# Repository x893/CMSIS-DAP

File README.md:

CMSIS-DAP Version 0.01
----------------------

See Readme.htm for details

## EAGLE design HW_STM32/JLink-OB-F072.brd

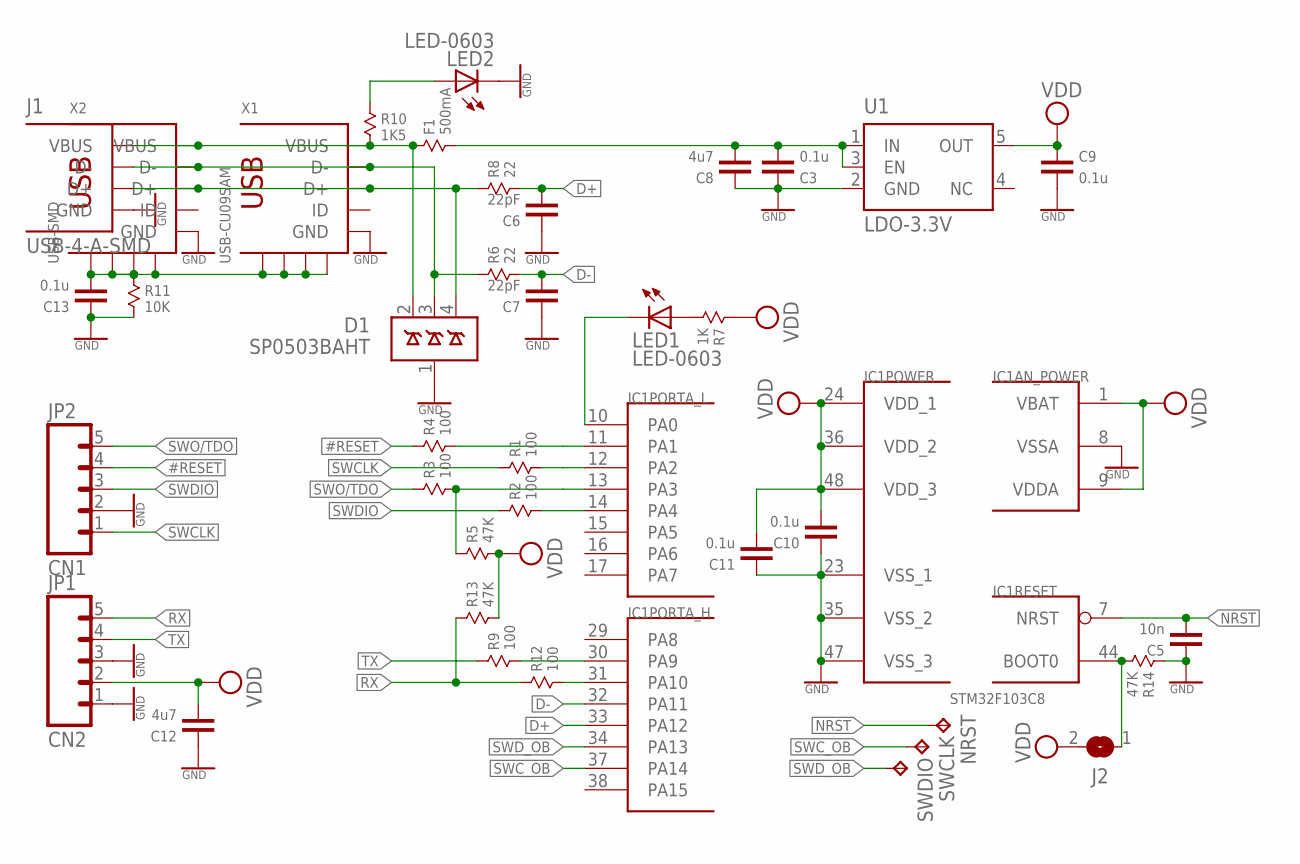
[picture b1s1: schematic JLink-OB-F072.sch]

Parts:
C3, C9, C10, C11, C13: 0.1u; 0603
C5: 10n; 0603
C6, C7: 22pF; 0603
C8, C12: 4u7; 0603
D1: SP0503BAHT; SOT143
F1: 500mA; 0805
IC1: STM32F103C8; TQFP48
J1: USB-4-A-SMD; USB-A-SMD
J2: JUMPER2-0402-NC; JUMPER2-0402_NC
JP1: CN2; 1X05
JP2: CN1; 1X05
LED1, LED2: LED-0603; CHIPLED_0603
NRST: TPTP10R; TP10R
R1, R2, R3, R4, R9, R12: 100; 0603
R5, R13, R14: 47K; 0603
R6, R8: 22; 0603
R7: 1K; 0603
R10: 1K5; 0603
R11: 10K; 0603
SWCLK: TPTP10R; TP10R
SWDIO: TPTP10R; TP10R
U1: LDO-3.3V; SOT23-5
X1: USB-CU09SAM; CU09SAM
X2: USB-SMD; USB-MINIB

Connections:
#RESET: JP2.4, R4.1
#RESETR: IC1.11 (PA1), R4.2
D+: C6.1, IC1.33 (PA12), R8.2
D-: C7.1, IC1.32 (PA11), R6.2
GND: C3.2, C5.2, C6.2, C7.2, C8.2, C9.1, C10.2, C11.2, C12.2, C13.2, D1.1 (GND), IC1.8 (VSSA), IC1.23 (VSS_1), IC1.35 (VSS_2), IC1.47 (VSS_3), J1.GND, JP1.1, JP1.3, JP2.2, LED2.C, R11.2, R14.1, U1.2 (GND), X1.5 (GND), X2.GND
unnamed: LED1.A, R7.2
unnamed: D1.4 (D3), J1.D+, R8.1, X1.3 (D+), X2.D+
unnamed: IC1.10 (PA0), LED1.C
unnamed: D1.3 (D2), J1.D-, R6.1, X1.2 (D-), X2.D-
unnamed: IC1.30 (PA9), R9.2
unnamed: IC1.31 (PA10), R12.2
unnamed: LED2.A, R10.1
unnamed: C3.1, C8.1, F1.2, U1.1 (IN), U1.3 (EN)
unnamed: IC1.44 (BOOT0), J2.1, R14.2
unnamed: C13.1, R11.1, X1.GND@1 (GND), X1.GND@2 (GND), X1.GND@3 (GND), X1.GND@4 (GND), X2.GND@1 (GND), X2.GND@2 (GND), X2.GND@3 (GND), X2.GND@4 (GND)
NRST: C5.1, IC1.7 (NRST), NRST.TP
RX: JP1.5, R12.1, R13.1
SWCLK: JP2.1, R1.1
SWCLKR: IC1.12 (PA2), R1.2
SWC_OB: IC1.37 (PA14), SWCLK.TP
SWDIO: JP2.3, R2.1
SWDIOR: IC1.14 (PA4), R2.2
SWD_OB: IC1.34 (PA13), SWDIO.TP
SWO/TDO: JP2.5, R3.1
SWOR: IC1.13 (PA3), R3.2, R5.1
TX: JP1.4, R9.1
VBUS: D1.2 (D1), F1.1, J1.VUSB (VBUS), R10.2, X1.1 (VBUS), X2.VBUS
VDD: C9.2, C10.1, C11.1, C12.1, IC1.1 (VBAT), IC1.9 (VDDA), IC1.24 (VDD_1), IC1.36 (VDD_2), IC1.48 (VDD_3), J2.2, JP1.2, R5.2, R7.1, R13.2, U1.5 (OUT)

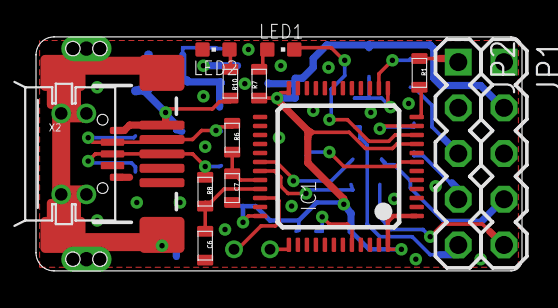
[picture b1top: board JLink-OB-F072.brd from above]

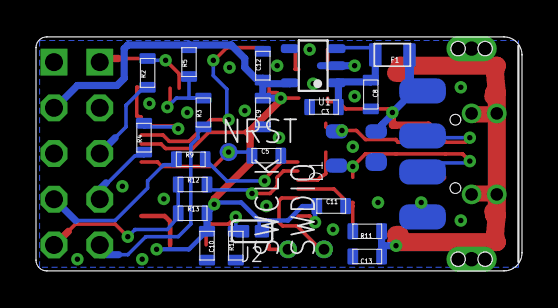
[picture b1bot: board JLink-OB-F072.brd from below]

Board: 2 copper layers, 27.0 x 13.0 mm, 39 parts (25 on the bottom side), 28 nets.

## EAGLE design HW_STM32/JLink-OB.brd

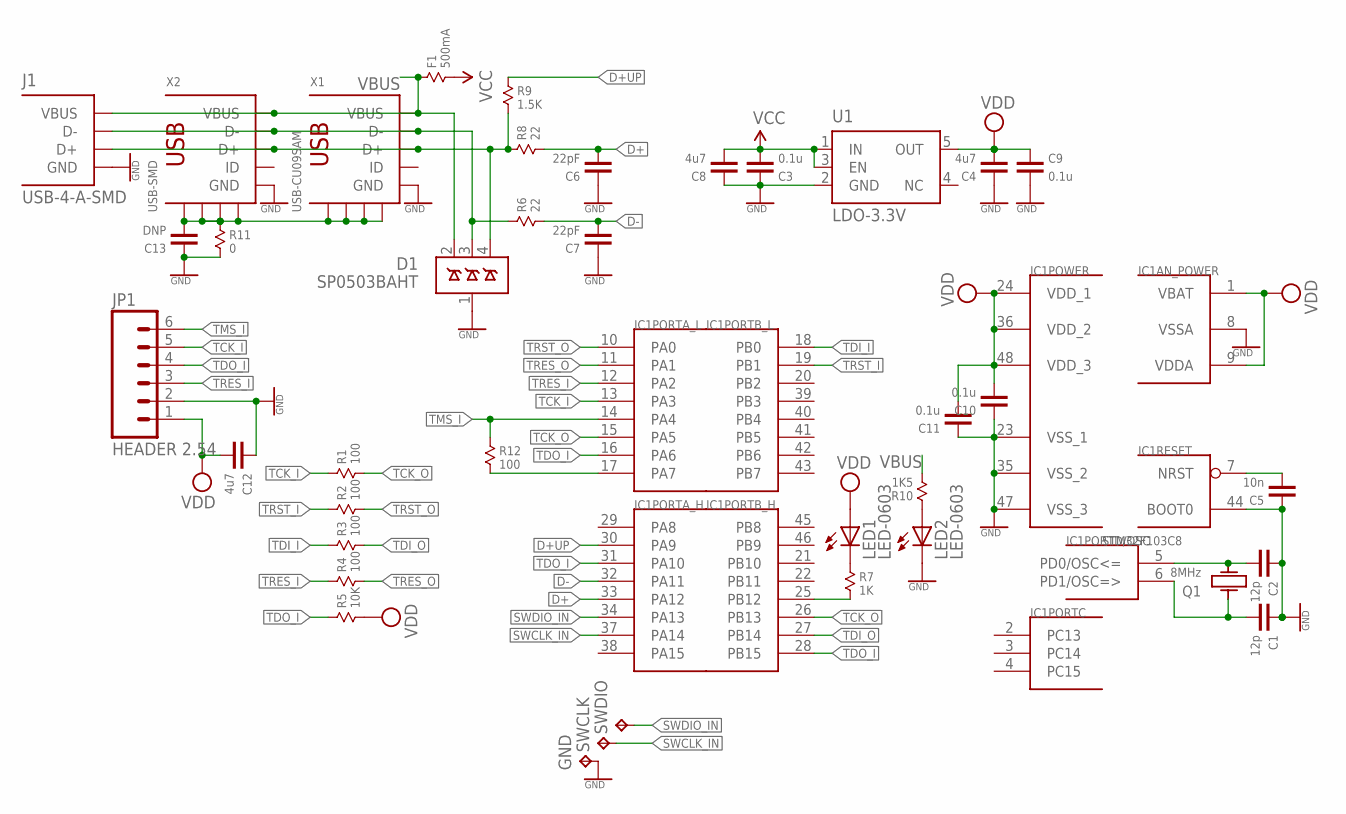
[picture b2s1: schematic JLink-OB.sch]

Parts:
C1, C2: 12p; 0603
C3, C9, C10, C11: 0.1u; 0603
C4, C8, C12: 4u7; 0603
C5: 10n; 0603
C6, C7: 22pF; 0603
C13: DNP; 0603
D1: SP0503BAHT; SOT143
F1: 500mA; 0805
GND: TPTP12R; TP12R
IC1: STM32F103C8; TQFP48
J1: USB-4-A-SMD; USB-A-SMD
JP1: HEADER 2.54; 1X06
LED1, LED2: LED-0603; CHIPLED_0603
Q1: 8MHz; KX-9A
R1, R2, R3, R4, R12: 100; 0603
R5: 10K; 0603
R6, R8: 22; 0603
R7: 1K; 0603
R9: 1.5K; 0603
R10: 1K5; 0603
R11: 0; 0603
SWCLK: TPTP12R; TP12R
SWDIO: TPTP12R; TP12R
U1: LDO-3.3V; SOT23-5
X1: USB-CU09SAM; CU09SAM
X2: USB-SMD; USB-MINIB

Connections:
D+: C6.1, IC1.33 (PA12), R8.2
D+UP: IC1.30 (PA9), R9.1
D-: C7.1, IC1.32 (PA11), R6.2
GND: C1.2, C2.2, C3.2, C4.2, C5.2, C6.2, C7.2, C8.2, C9.1, C10.2, C11.2, C12.2, C13.2, D1.1 (GND), GND.TP, IC1.8 (VSSA), IC1.23 (VSS_1), IC1.35 (VSS_2), IC1.44 (BOOT0), IC1.47 (VSS_3), J1.GND, JP1.2, LED2.C, R11.2, U1.2 (GND), X1.5 (GND), X2.GND
unnamed: C5.1, IC1.7 (NRST)
unnamed: D1.4 (D3), J1.D+, R8.1, R9.2, X1.3 (D+), X2.D+
unnamed: IC1.25 (PB12), R7.2
unnamed: D1.3 (D2), J1.D-, R6.1, X1.2 (D-), X2.D-
unnamed: C2.1, IC1.5 (PD0/OSC<=), Q1.3 (2)
unnamed: C1.1, IC1.6 (PD1/OSC=>), Q1.1
unnamed: LED2.A, R10.1
unnamed: LED1.C, R7.1
unnamed: C13.1, R11.1, X1.GND@1 (GND), X1.GND@2 (GND), X1.GND@3 (GND), X1.GND@4 (GND), X2.GND@1 (GND), X2.GND@2 (GND), X2.GND@3 (GND), X2.GND@4 (GND)
SWCLK_IN: IC1.37 (PA14), SWCLK.TP
SWDIO_IN: IC1.34 (PA13), SWDIO.TP
TCK_I: IC1.13 (PA3), JP1.5, R1.1
TCK_O: IC1.15 (PA5), IC1.26 (PB13), R1.2
TDI_I: IC1.18 (PB0), R3.1
TDI_O: IC1.27 (PB14), R3.2
TDO_I: IC1.16 (PA6), IC1.28 (PB15), IC1.31 (PA10), JP1.4, R5.1
TMS_I: IC1.14 (PA4), JP1.6, R12.1
TMS_O: IC1.17 (PA7), R12.2
TRES_I: IC1.12 (PA2), JP1.3, R4.1
TRES_O: IC1.11 (PA1), R4.2
TRST_I: IC1.19 (PB1), R2.1
TRST_O: IC1.10 (PA0), R2.2
VBUS: D1.2 (D1), F1.1, J1.VUSB (VBUS), R10.2, X1.1 (VBUS), X2.VBUS
VCC: C3.1, C8.1, F1.2, U1.1 (IN), U1.3 (EN)
VDD: C4.1, C9.2, C10.1, C11.1, C12.1, IC1.1 (VBAT), IC1.9 (VDDA), IC1.24 (VDD_1), IC1.36 (VDD_2), IC1.48 (VDD_3), JP1.1, LED1.A, R5.2, U1.5 (OUT)

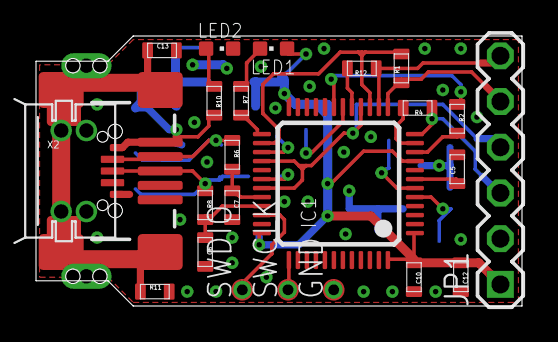
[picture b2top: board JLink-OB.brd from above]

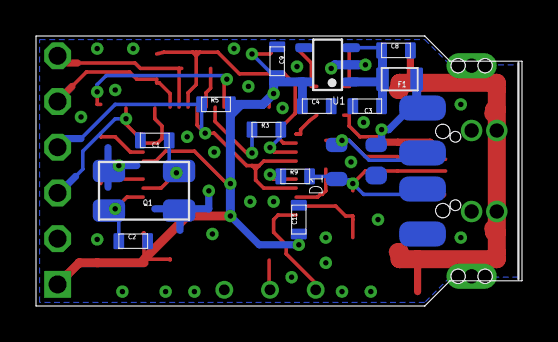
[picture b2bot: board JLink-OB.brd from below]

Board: 2 copper layers, 27.0 x 15.0 mm, 39 parts (15 on the bottom side), 29 nets.

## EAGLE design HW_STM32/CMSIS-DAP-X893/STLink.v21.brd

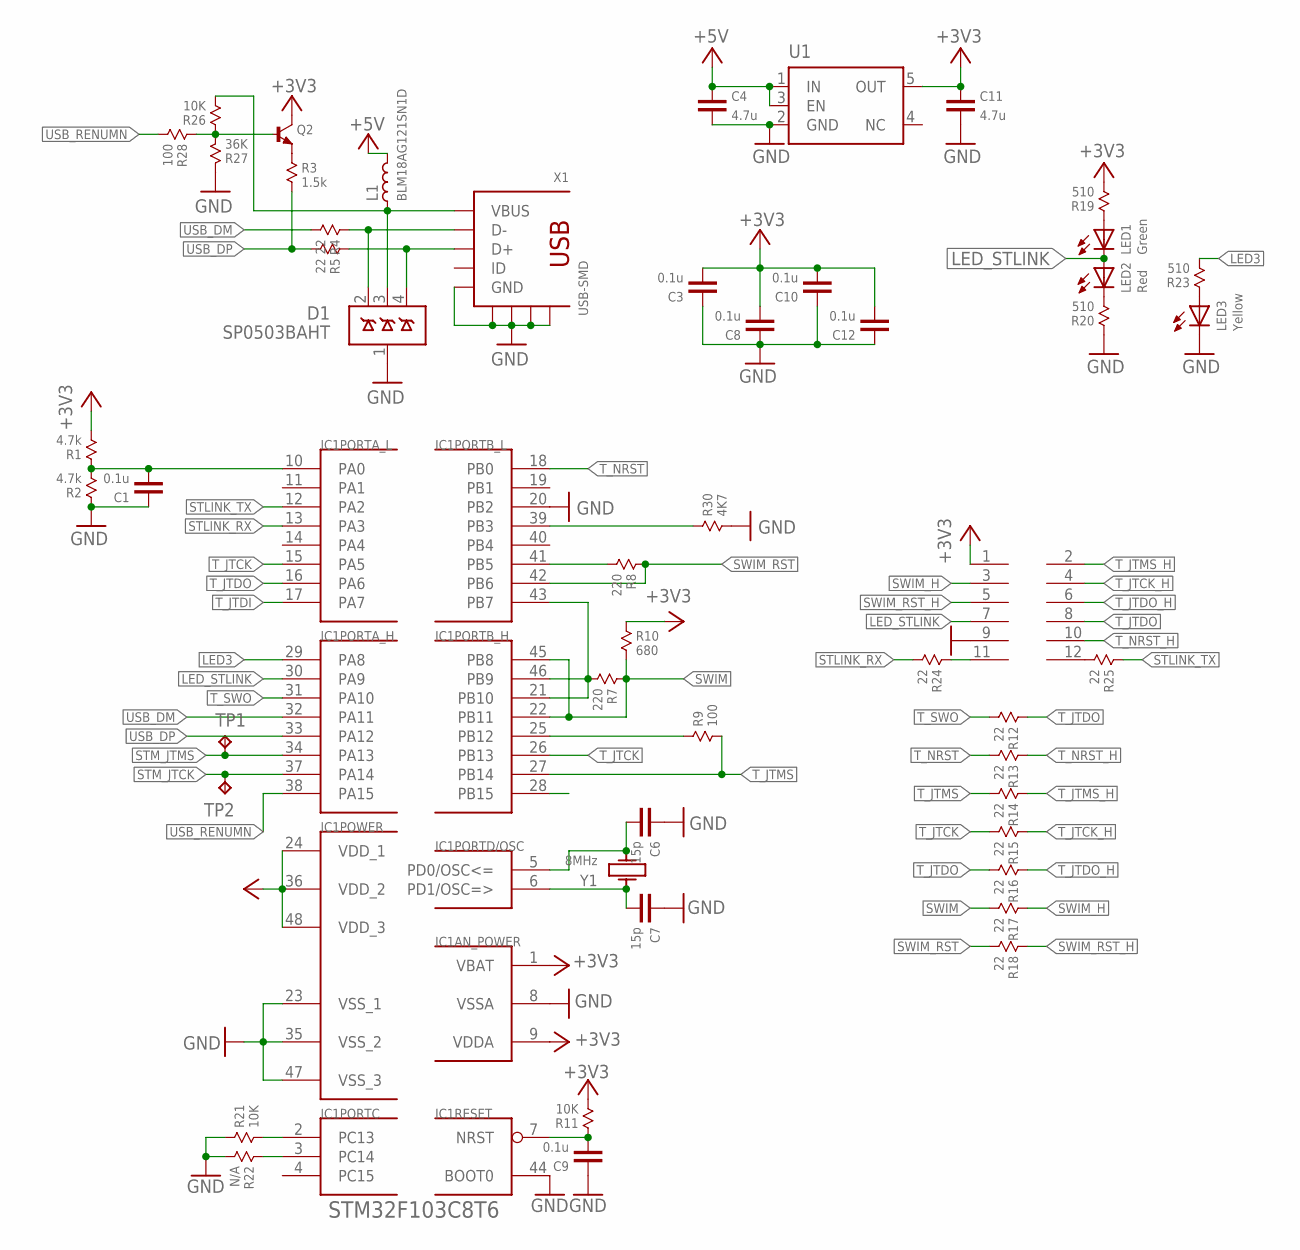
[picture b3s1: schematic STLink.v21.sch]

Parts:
C1, C3, C8, C9, C10, C12: 0.1u; 0603
C4, C11: 4.7u; 0603
C6, C7: 15p; 0603
CN2: M06X2; PLANAR-6X2
D1: SP0503BAHT; SOT143
IC1: STM32F103C8T6; TQFP48
L1: BLM18AG121SN1D; 0603
LED1: Green; CHIP-LED0603
LED2: Red; CHIP-LED0603
LED3: Yellow; CHIP-LED0603
Q2: NPNBC847; SOT-23
R1, R2: 4.7k; 0603
R3: 1.5k; 0603
R4, R5, R12, R13, R14, R15, R16, R17, R18, R24, R25: 22; 0603
R7, R8: 220; 0603
R9, R28: 100; 0603
R10: 680; 0603
R11, R21, R26: 10K; 0603
R19, R20, R23: 510; 0603
R22: N/A; 0603
R27: 36K; 0603
R30: 4K7; 0603
TP1, TP2: TPTP10R; TP10R
U1: TPS73033; SOT23-5
X1: USB-SMD; USB-MINIB
Y1: 8MHz; C0532

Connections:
+3V3: C3.1, C8.1, C10.1, C11.2, C12.1, CN2.1, IC1.1 (VBAT), IC1.9 (VDDA), IC1.24 (VDD_1), IC1.36 (VDD_2), IC1.48 (VDD_3), Q2.3 (C), R1.2, R10.1, R11.2, R19.2, U1.5 (OUT)
+5V: C4.2, L1.2, U1.1 (IN), U1.3 (EN)
AIN1: C1.1, IC1.10 (PA0), R1.1, R2.2
GND: C1.2, C3.2, C4.1, C6.2, C7.2, C8.2, C9.2, C10.2, C11.1, C12.2, CN2.9, D1.1 (GND), IC1.8 (VSSA), IC1.20 (PB2), IC1.23 (VSS_1), IC1.35 (VSS_2), IC1.44 (BOOT0), IC1.47 (VSS_3), LED3.C, R2.1, R20.1, R21.1, R22.2, R27.1, R30.2, U1.2 (GND), X1.GND, X1.GND@1 (GND), X1.GND@2 (GND), X1.GND@3 (GND), X1.GND@4 (GND)
LED3: IC1.29 (PA8), R23.2
LED_STLINK: CN2.7, IC1.30 (PA9), LED1.C, LED2.A
unnamed: C6.1, IC1.5 (PD0/OSC<=), Y1.3 (2)
unnamed: C7.1, IC1.6 (PD1/OSC=>), Y1.1
unnamed: C9.1, IC1.7 (NRST), R11.1
unnamed: IC1.39 (PB3), R30.1
unnamed: D1.2 (D1), R4.1, X1.D-
unnamed: D1.4 (D3), R5.1, X1.D+
unnamed: LED2.C, R20.2
unnamed: LED1.A, R19.1
unnamed: D1.3 (D2), L1.1, R26.2, X1.VBUS
unnamed: CN2.11, R24.1
unnamed: CN2.12, R25.2
unnamed: LED3.A, R23.1
unnamed: Q2.2 (E), R3.1
unnamed: IC1.2 (PC13), R21.2
unnamed: IC1.3 (PC14), R22.1
unnamed: Q2.1 (B), R26.1, R27.2, R28.1
STLINK_RX: IC1.13 (PA3), R24.2
STLINK_TX: IC1.12 (PA2), R25.1
STM_JTCK: IC1.37 (PA14), TP2.TP
STM_JTMS: IC1.34 (PA13), TP1.TP
SWIM: IC1.22 (PB11), IC1.45 (PB8), R7.1, R10.2, R17.2
SWIM_H: CN2.3, R17.1
SWIM_IN: IC1.21 (PB10), IC1.43 (PB7), IC1.46 (PB9), R7.2
SWIM_RST: IC1.42 (PB6), R8.1, R18.2
SWIM_RST_H: CN2.5, R18.1
SWIM_RST_IN: IC1.41 (PB5), R8.2
T_JTCK: IC1.15 (PA5), IC1.26 (PB13), R15.2
T_JTCK_H: CN2.4, R15.1
T_JTDI: IC1.17 (PA7)
T_JTDO: CN2.8, IC1.16 (PA6), R12.1, R16.2
T_JTDO_H: CN2.6, R16.1
T_JTMS: IC1.27 (PB14), R9.2, R14.2
T_JTMS_H: CN2.2, R14.1
T_NRST: IC1.18 (PB0), R13.2
T_NRST_H: CN2.10, R13.1
T_SWDIO_IN: IC1.25 (PB12), R9.1
T_SWO: IC1.31 (PA10), R12.2
USB_DM: IC1.32 (PA11), R4.2
USB_DP: IC1.33 (PA12), R3.2, R5.2
USB_RENUMN: IC1.38 (PA15), R28.2

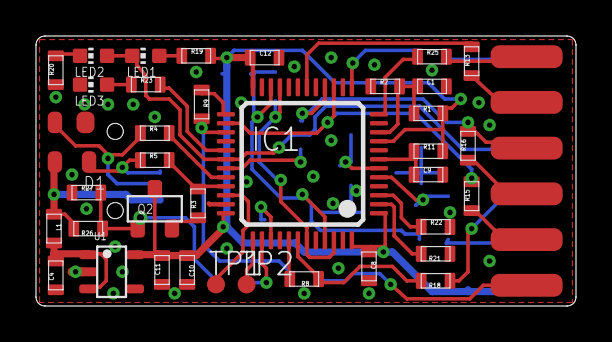
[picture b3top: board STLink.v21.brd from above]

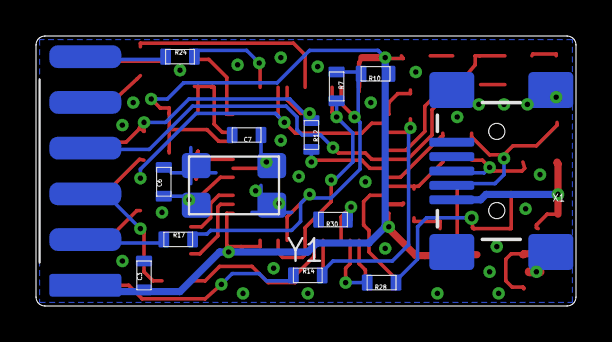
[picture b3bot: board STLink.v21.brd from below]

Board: 2 copper layers, 30.0 x 15.0 mm, 51 parts (14 on the bottom side), 45 nets.

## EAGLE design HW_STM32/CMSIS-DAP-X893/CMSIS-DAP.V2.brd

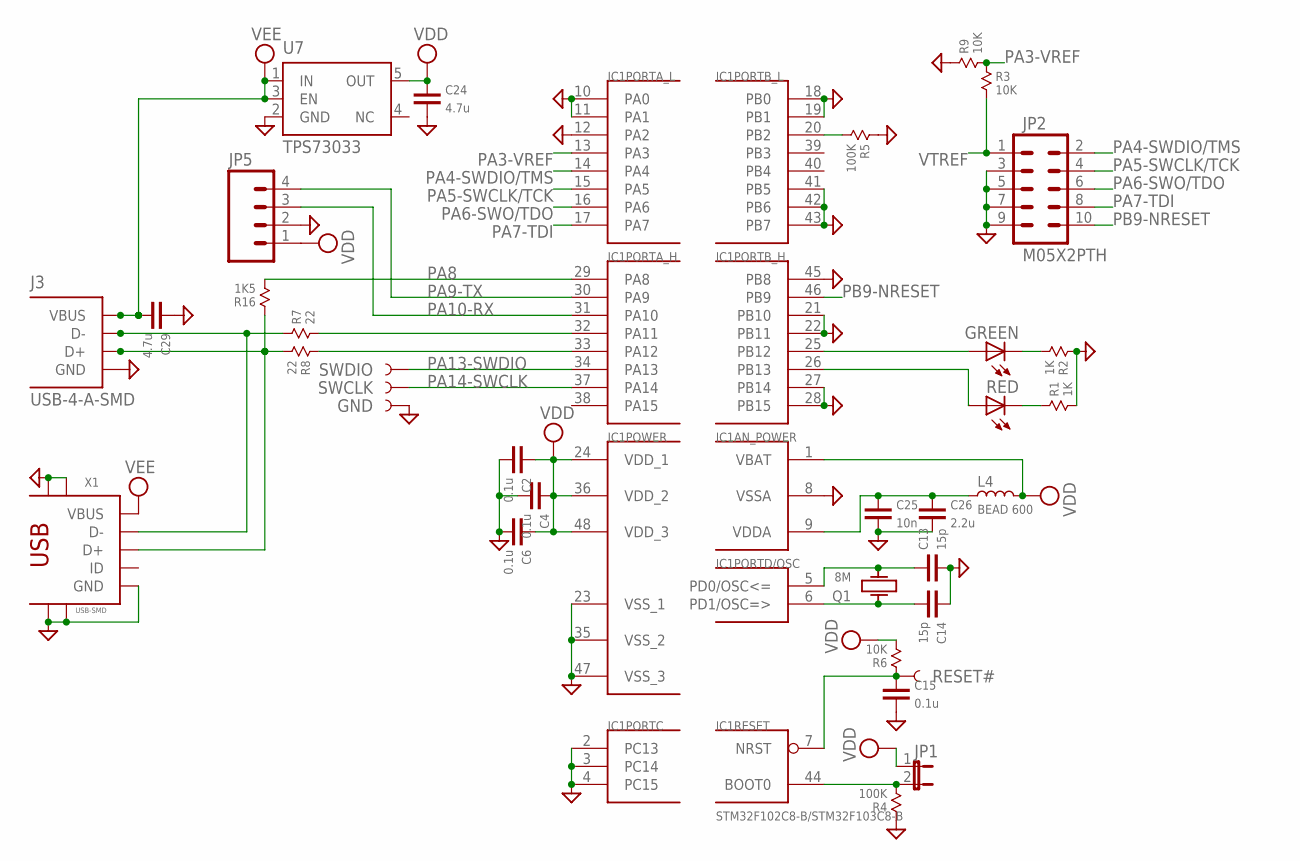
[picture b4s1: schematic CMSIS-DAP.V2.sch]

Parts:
C2, C4, C6, C15: 0.1u; 0603
C13, C14: 15p; 0603
C24, C29: 4.7u; 0603
C25: 10n; 0603
C26: 2.2u; 0603
GND: TEST-POINT1; PAD.1X1
GREEN: LEDCHIPLED_0603; CHIPLED_0603
IC1: STM32F102C8-B/STM32F103C8-B; TQFP48
J3: USB-4-A-SMD; USB-A-SMD
JP1: JUMPER-2SMD-NO; SJ_2S-NO
JP2: M05X2PTH; AVR_ICSP
JP5: M04PTH; 1X04
L4: BEAD 600; 0603
Q1: 8M; KX-9A
R1, R2: 1K; 0603
R3, R6, R9: 10K; 0603
R4, R5: 100K; 0603
R7, R8: 22; 0603
R16: 1K5; 0603
RED: LEDCHIPLED_0603; CHIPLED_0603
RESET#: TEST-POINT3; PAD.03X.03
SWCLK: TEST-POINT1; PAD.1X1
SWDIO: TEST-POINT1; PAD.1X1
U7: TPS73033; SOT23-5
X1: USB-SMD; USB-MINIB

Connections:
BOOT0: IC1.44 (BOOT0), JP1.2, R4.2
GND: C2.1, C4.1, C6.1, C13.1, C14.2, C15.1, C24.1, C25.1, C26.1, C29.2, GND.P$1, IC1.2 (PC13), IC1.3 (PC14), IC1.4 (PC15), IC1.8 (VSSA), IC1.10 (PA0), IC1.11 (PA1), IC1.12 (PA2), IC1.18 (PB0), IC1.19 (PB1), IC1.21 (PB10), IC1.22 (PB11), IC1.23 (VSS_1), IC1.27 (PB14), IC1.28 (PB15), IC1.35 (VSS_2), IC1.41 (PB5), IC1.42 (PB6), IC1.43 (PB7), IC1.45 (PB8), IC1.47 (VSS_3), J3.GND, JP2.3, JP2.5, JP2.7, JP2.9, JP5.2, R1.2, R2.1, R4.1, R5.1, R9.1, U7.2 (GND), X1.GND, X1.GND@1 (GND), X1.GND@2 (GND), X1.GND@3 (GND), X1.GND@4 (GND)
unnamed: R1.1, RED.C
unnamed: C25.2, C26.2, IC1.9 (VDDA), L4.1
unnamed: J3.D-, R7.1, X1.D-
unnamed: GREEN.C, R2.2
unnamed: J3.D+, R8.2, R16.1, X1.D+
OSCIN: C14.1, IC1.6 (PD1/OSC=>), Q1.1
OSCOUT: C13.2, IC1.5 (PD0/OSC<=), Q1.3 (2)
PA3-VREF: IC1.13 (PA3), R3.1, R9.2
PA4-SWDIO/TMS: IC1.14 (PA4), JP2.2
PA5-SWCLK/TCK: IC1.15 (PA5), JP2.4
PA6-SWO/TDO: IC1.16 (PA6), JP2.6
PA7-TDI: IC1.17 (PA7), JP2.8
PA8: IC1.29 (PA8), R16.2
PA9-TX: IC1.30 (PA9), JP5.4
PA10-RX: IC1.31 (PA10), JP5.3
PA11: IC1.32 (PA11), R7.2
PA12: IC1.33 (PA12), R8.1
PA13-SWDIO: IC1.34 (PA13), SWDIO.P$1
PA14-SWCLK: IC1.37 (PA14), SWCLK.P$1
PB2/BOOT1: IC1.20 (PB2), R5.2
PB9-NRESET: IC1.46 (PB9), JP2.10
PB12: GREEN.A, IC1.25 (PB12)
PB13: IC1.26 (PB13), RED.A
RESET#: C15.2, IC1.7 (NRST), R6.1, RESET#.P$1
VDD: C2.2, C4.2, C6.2, C24.2, IC1.1 (VBAT), IC1.24 (VDD_1), IC1.36 (VDD_2), IC1.48 (VDD_3), JP1.1, JP5.1, L4.2, R6.2, U7.5 (OUT)
VEE: C29.1, J3.VUSB (VBUS), U7.1 (IN), U7.3 (EN), X1.VBUS
VTREF: JP2.1, R3.2

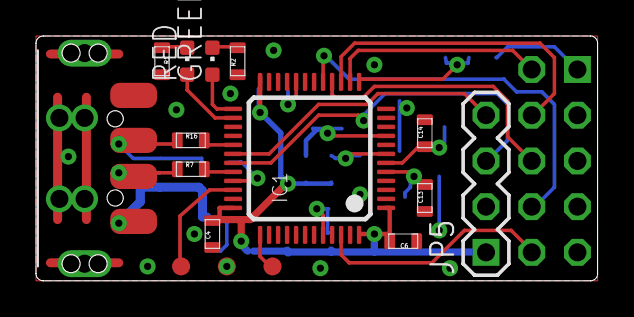
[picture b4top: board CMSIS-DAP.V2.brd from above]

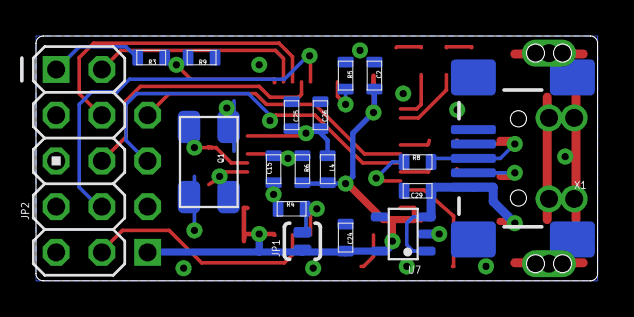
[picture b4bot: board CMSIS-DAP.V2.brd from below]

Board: 2 copper layers, 31.2 x 13.6 mm, 35 parts (19 on the bottom side), 29 nets.

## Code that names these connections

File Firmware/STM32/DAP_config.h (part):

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#define PIN_MASK(pin)			(((uint16_t)0x01) << (pin))

typedef enum Pin_e {
	PA = 0x00, PA0 = 0x00, PA1, PA2, PA3, PA4, PA5, PA6, PA7, PA8, PA9, PA10, PA11, PA12, PA13, PA14, PA15,
	PB = 0x10, PB0 = 0x10, PB1, PB2, PB3, PB4, PB5, PB6, PB7, PB8, PB9, PB10, PB11, PB12, PB13, PB14, PB15,
	PC = 0x20, PC0 = 0x20, PC1, PC2, PC3, PC4, PC5, PC6, PC7, PC8, PC9, PC10, PC11, PC12, PC13, PC14, PC15,
	PD = 0x30, PD0 = 0x30, PD1, PD2,
} Pin_t;

// USART Port and I/O Pins
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of the same I/O port. The following SWDIO I/O Pin functions are provided:
 - \ref PIN_SWDIO_OUT_ENABLE to enable the output mode from the DAP hardware.
 - \ref PIN_SWDIO_OUT_DISABLE to enable the input mode to the DAP hardware.
 - \ref PIN_SWDIO_IN to read from the SWDIO I/O pin with utmost possible speed.
 - \ref PIN_SWDIO_OUT to write to the SWDIO I/O pin with utmost possible speed.
*/

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/** SWDIO I/O pin: Get Input (used in SWD mode only).
\return Current status of the SWDIO DAP hardware I/O pin.
*/
__STATIC_INLINE uint8_t PIN_SWDIO_IN (void)
{
	if (PIN_SWDIO_TMS_PORT->IDR & PIN_SWDIO_TMS)
		return 1;
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
/** SWDIO I/O pin: Switch to Input mode (used in SWD mode only).
Configure the SWDIO DAP hardware I/O pin to input mode. This function is
called prior \ref PIN_SWDIO_IN function calls.
*/
__STATIC_INLINE void PIN_SWDIO_OUT_DISABLE(void)
{
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
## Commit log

2013-01-28 Initial
2013-01-28 Add Readme.txt
2013-01-29 Git fixes
2013-02-07 Move license to EOF
2013-03-05 Change to composite device CDC + HID. Additional serial port for general purpose.
2013-04-12 Add COM support
2013-06-05 Hardware version 2 of STM32 small debug adapter. Fixup some codes.
2013-06-20 Fixup
2013-07-23 Fix RESET pin
2013-07-25 Change mode for unused pins
2013-08-14 No changes
2014-01-31 Add hex files, pins definition inside source.
2014-04-25 Add usb_lib.c and shematic in pdf
2014-04-25 Add sources for USB stack from Keil (see #issue 1). Thanks to J Alvarez @ Micromint.
2014-04-25 Add Readme.md
2014-11-15 Cosmetic fixes
2014-11-15 Add HEX file
2015-02-17 Add STM32F102CB for V2 PCB
2015-04-15 Initial commit for V3
2015-05-08 Add support for ST-Link V2 hardware (V3)
2015-07-23 Add CMSIS-DAP for STLink V2.1 and STLink v2.1 mini adapter.
2015-10-05 Add CMSIS-DAP-STLINK21.hex
2016-01-16 Add STLink.v21.pdf schematic
2016-01-17 Add JLink-OB PCB
2016-11-28 Add JLink-OB-F072 hardware
2020-12-21 docs: fix simple typo, treshold -> threshold
    There is a small typo in Firmware/LPC-Link-II/usbd_LPC43xx_USB0.c.
    Should read `threshold` rather than `treshold`.

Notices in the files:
Firmware/STM32/DAP_config.h:
Copyright (C) 2012 ARM Limited. All rights reserved.
parts and their libraries:
SparkFun-Aesthetics: Licensing: CC v3.0 Share-Alike You are welcome to use this library for commercial purposes.
